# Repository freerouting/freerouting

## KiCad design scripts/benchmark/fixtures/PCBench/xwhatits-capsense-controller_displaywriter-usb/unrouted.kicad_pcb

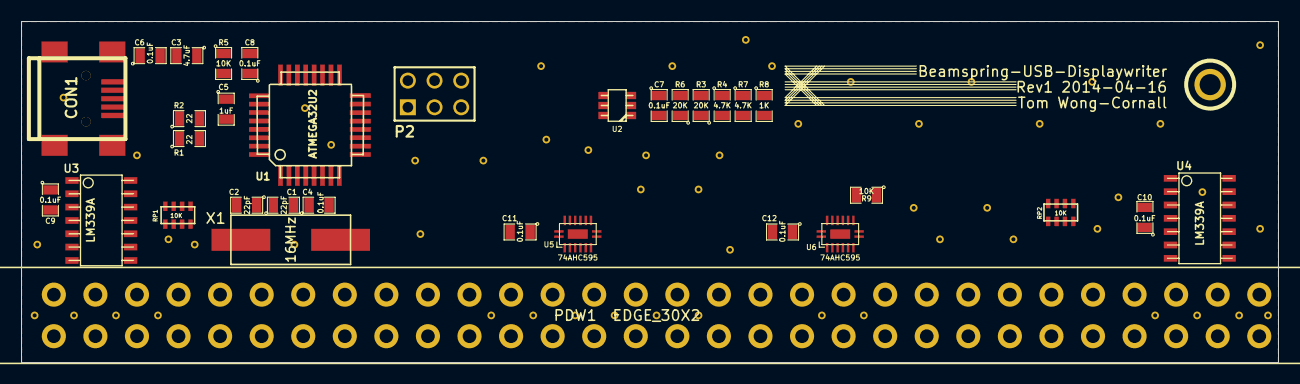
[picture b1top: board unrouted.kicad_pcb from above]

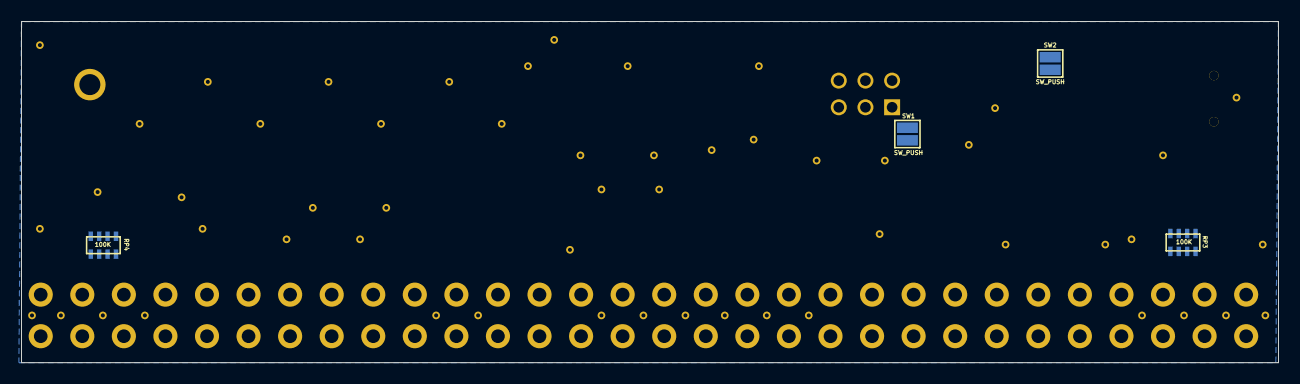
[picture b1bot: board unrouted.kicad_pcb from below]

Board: 2 copper layers, 119.8 x 32.5 mm, 92 parts (4 on the bottom side), 54 nets, no tracks yet.

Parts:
., ._2, ._3, ._4, ._5, ._6, ._7, ._8, ._9, ._10, ._11, ._12, ._13, ._14, ._15, ._16, ._17, ._18, ._19, ._20, ._21, ._22, ._23, ._24, ._25, ._26, ._27, ._28, ._29, ._30, ._31, ._32, ._33, ._34, ._35, ._36, ._37, ._38, ._39, ._40, ._41, ._42, ._43, ._44, ._45, ._46, ._47, ._48, ._49, ._50, ._51, ._52, ._53, ._54: .; Via
C1, C2: 22pF; SM0805
C3: 4.7uF; SM0805
C4, C6, C7, C8, C9, C10, C11, C12: 0.1uF; SM0805
C5: 1uF; SM0805
CON1: USB-MINI-B; USB_MINI_B
P2: CONN_3X2; pin_array_3x2
P3: Chassis GND; 1pin
PDW1: EDGE_30X2; 805_396_30x2_pins
R1, R2: 22; SM0805
R3, R6: 20K; SM0805
R4, R7: 4.7K; SM0805
R5, R9: 10K; SM0805
R8: 1K; SM0805
RP1, RP2: 10K; RPACK_1206
RP3, RP4: 100K; RPACK_1206
SW1, SW2: SW_PUSH; TEST_BRIDGE_SM
U1: ATMEGA32U2; TQFP32
U2: DAC101S101; tsot-6
U3, U4: LM339A; so-14
U5, U6: 74AHC595; DHVQFN16
X1: 16MHz; HC49US

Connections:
/SPI_MOSI: U1.16, U2.4
/SPI_SCLK: U1.15, U2.5
/SPI_SS: U1.14, U2.6
Col1: PDW1.10, PDW1.40, U5.15
Col2: PDW1.11, PDW1.41, U5.1
Col3: PDW1.12, PDW1.42, U5.2
Col4: PDW1.13, PDW1.43, U5.3
Col5: PDW1.14, PDW1.44, U5.4
Col6: PDW1.15, PDW1.45, U5.5
Col7: PDW1.16, PDW1.46, U5.6
Col8: PDW1.17, PDW1.47, U5.7
Col9: PDW1.18, PDW1.48, U6.15
Col10: PDW1.19, PDW1.49, U6.1
Col11: PDW1.20, PDW1.50, U6.2
Col12: PDW1.21, PDW1.51, U6.3
GND: C1.1, C2.1, C3.2, C4.1, C5.2, C6.2, C7.2, C8.2, C9.1, C10.1, C11.2, C12.2, CON1.5, P2.6, P3.1, PDW1.5, PDW1.9, PDW1.22, PDW1.26, PDW1.35, PDW1.39, PDW1.52, PDW1.56, R4.2, R8.2, SW1.1, SW2.2, U1.3, U1.28, U2.2, U3.12, U4.12, U5.8, U6.8
unnamed: U5.9, U6.14
unnamed: C6.1, CON1.6
unnamed: R6.1, U2.1
unnamed: C2.2, U1.1, X1.2
unnamed: C5.1, U1.27
unnamed: C8.1, R5.2, SW2.1, U1.24
unnamed: R3.1, R4.1, R6.2, U3.4, U3.6, U3.8, U3.10, U4.4, U4.6, U4.8, U4.10
unnamed: CON1.3, R2.1
unnamed: CON1.2, R1.1
unnamed: R2.2, U1.29
unnamed: R1.2, U1.30
unnamed: P2.5, U1.19
unnamed: P2.3, U1.18
unnamed: P2.2, U1.21
unnamed: P2.4, U1.20
unnamed: R7.2, R8.1, RP3.1, RP3.2, RP3.3, RP3.4, RP4.1, RP4.2, RP4.3, RP4.4
unnamed: C1.2, U1.2, X1.1
Row1: PDW1.1, PDW1.31, RP3.8, U3.5
Row2: PDW1.2, PDW1.32, RP3.7, U3.7
Row3: PDW1.3, PDW1.33, RP3.6, U3.9
Row4: PDW1.4, PDW1.34, RP3.5, U3.11
Row5: PDW1.27, PDW1.57, RP4.8, U4.5
Row6: PDW1.28, PDW1.58, RP4.7, U4.7
Row7: PDW1.29, PDW1.59, RP4.6, U4.9
Row8: PDW1.30, PDW1.60, RP4.5, U4.11
RowOP1: RP1.1, U1.26, U3.2
RowOP2: RP1.2, U1.25, U3.1
RowOP3: RP1.3, U1.23, U3.14
RowOP4: RP1.4, U1.22, U3.13
RowOP5: RP2.1, U1.6, U4.2
RowOP6: RP2.2, U1.7, U4.1
RowOP7: RP2.3, U1.8, U4.14
RowOP8: RP2.4, U1.9, U4.13
SR_DS: U1.10, U5.14
SR_OE: U1.11, U5.13, U6.13
SR_SHCP: R9.2, SW1.2, U1.13, U5.11, U6.11
SR_STCP: U1.12, U5.12, U6.12
VCC: C3.1, C4.2, C7.1, C9.2, C10.2, C11.1, C12.1, CON1.1, P2.1, R3.2, R5.1, R7.1, R9.1, RP1.5, RP1.6, RP1.7, RP1.8, RP2.5, RP2.6, RP2.7, RP2.8, U1.4, U1.31, U1.32, U2.3, U3.3, U4.3, U5.10, U5.16, U6.10, U6.16
